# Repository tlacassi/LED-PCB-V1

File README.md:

# LED-PCB-V1

Une vidéo qui explique le minimum nécessaire pour faire tourner l'ESP sur un pcb : https://www.youtube.com/watch?v=tQ0dL_9M1wI&t=242s

Le projet WLED pour le soft et les intégrations : https://kno.wled.ge

Datasheet WS2815b : https://www.marutsu.co.jp/contents/shop/marutsu/datasheet/WS2815B.pdf

Datasheet ESP32 : https://www.espressif.com/sites/default/files/documentation/esp32-s3-wroom-1_wroom-1u_datasheet_en.pdf

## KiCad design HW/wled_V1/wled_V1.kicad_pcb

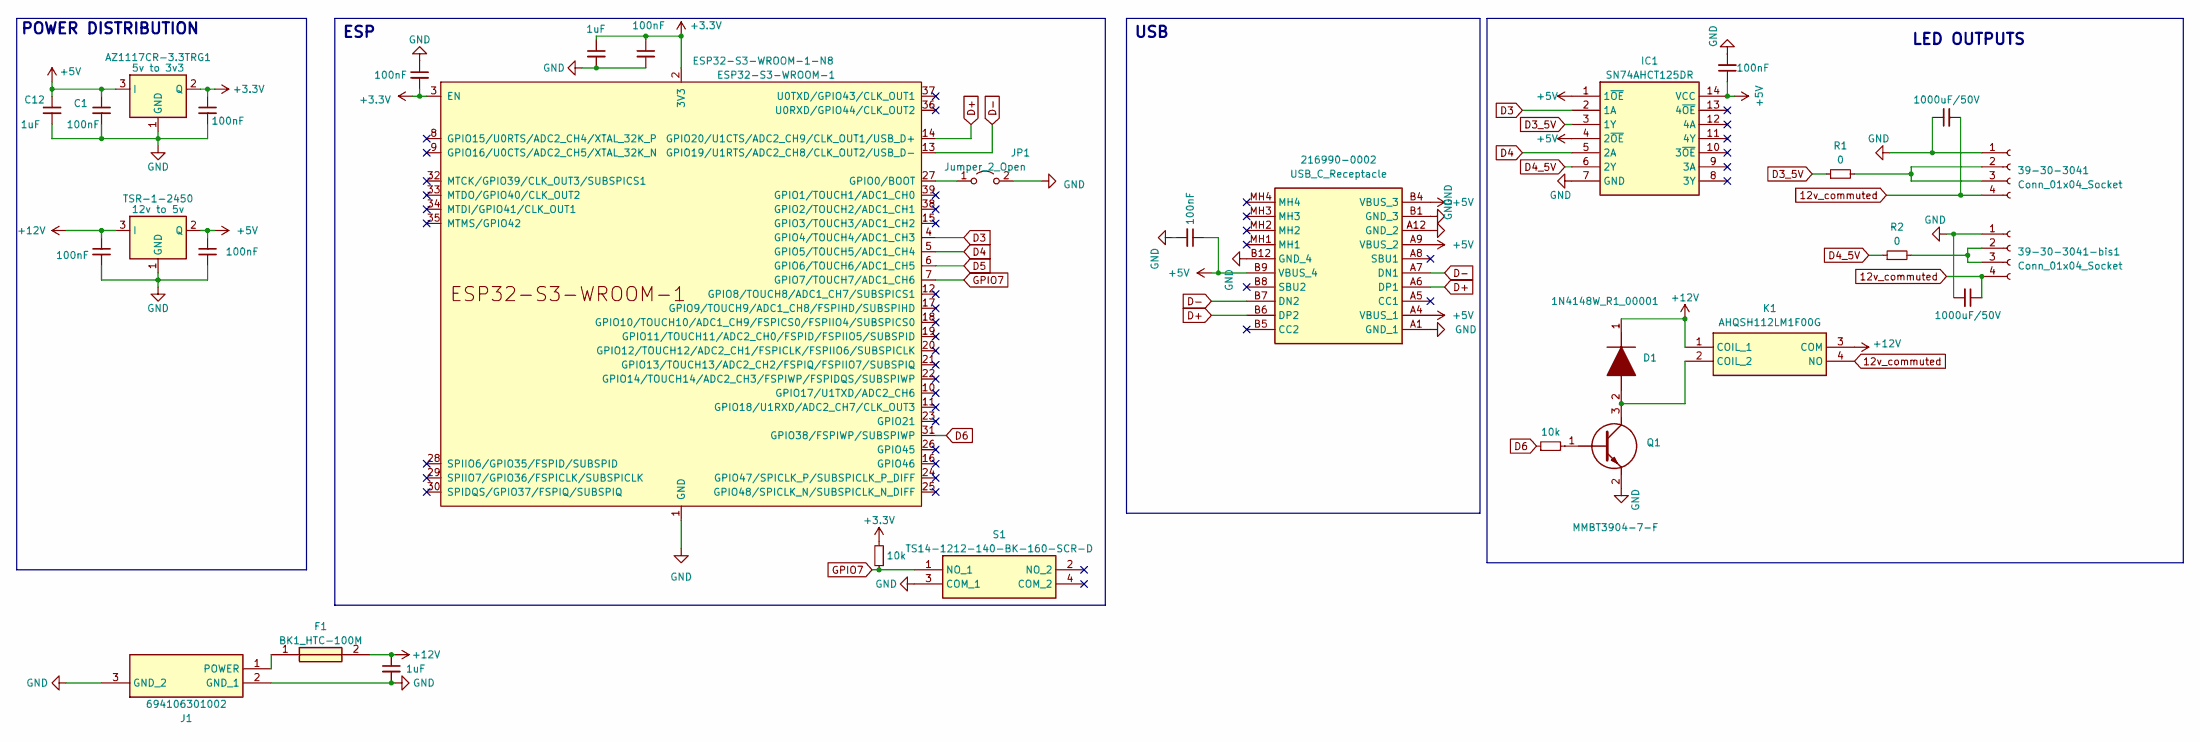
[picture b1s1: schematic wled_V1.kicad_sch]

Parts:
39-30-3041, 39-30-3041-bis1: Conn_01x04_Socket; 39303041
216990-0002: USB_C_Receptacle; 2169900002; Mouser Part Number 538-216990-0002
AZ1117CR-3.3TRG1: 5v to 3v3; AZ1117CR33TRG1
C1, C2, C3, C4, C6, C9, C11, C0402C103K1RACAUTO1: 100nF; CAPC1005X55N
C5, C8: 1000uF/50V; CAPAE1030X1050N
C12, C13, C14: 1uF; CAPC1005X55N
D1: 1N4148W_R1_00001; SOD3816X135N; Mouser Part Number 241-1N4148W_R1_00001
ESP32-S3-WROOM-1-N8: ESP32-S3-WROOM-1; ESP32S3WROOM1N8R8
F1: BK1_HTC-100M; BK1HTC100M; Mouser Part Number 504-BK1-HTC-100M
IC1: SN74AHCT125DR; SOIC127P600X175-14N; Mouser Part Number 595-SN74AHCT125DR
J1: 694106301002; 694106301002_1; Mouser Part Number 710-694106301002
JP1: Jumper_2_Open; SolderJumper-2_P1.3mm_Bridged2Bar_Pad1.0x1.5mm
K1: AHQSH112LM1F00G; Mouser Part Number 523-AHQSH112LM1F00G
Q1: MMBT3904-7-F; SOT96P240X110-3N; Mouser Part Number 621-MMBT3904-F
R1, R2: 0; R_0603_1608Metric_Pad0.98x0.95mm_HandSolder
RN73H1JTTD1002F1, RN73H1JTTD1002F50: 10k; R_0603_1608Metric_Pad0.98x0.95mm_HandSolder
S1: TS14-1212-140-BK-160-SCR-D; TS0266160BK260LCRD; Manufacturer_Part_Number TS14-1212-140-BK-160-SCR-D
TSR-1-2450: 12v to 5v; TSR12450

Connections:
12v_commuted: 39-30-3041.4, 39-30-3041-bis1.4, C5.1, C8.2, K1.4 (NO)
+3.3V: AZ1117CR-3.3TRG1.2 (Q), C2.1, C6.2, C14.1, C0402C103K1RACAUTO1.1, ESP32-S3-WROOM-1-N8.2 (3V3), ESP32-S3-WROOM-1-N8.3 (EN), RN73H1JTTD1002F1.2; also elsewhere on the board
+5V: 216990-0002.A4 (VBUS_1), 216990-0002.A9 (VBUS_2), 216990-0002.B4 (VBUS_3), 216990-0002.B9 (VBUS_4), AZ1117CR-3.3TRG1.3 (I), C1.1, C4.1, C9.1, C11.1, C12.1, IC1.1 (1~OE), IC1.4 (2~OE), IC1.14 (VCC), TSR-1-2450.2 (Q)
+12V: C3.1, C13.1, D1.1 (K), F1.2, K1.1 (COIL_1), K1.3 (COM), TSR-1-2450.3 (I)
D3: ESP32-S3-WROOM-1-N8.4 (GPIO4/TOUCH4/ADC1_CH3), IC1.2 (1A)
D3_5V: IC1.3 (1Y), R1.1
D4: ESP32-S3-WROOM-1-N8.5 (GPIO5/TOUCH5/ADC1_CH4), IC1.5 (2A)
D4_5V: IC1.6 (2Y), R2.1
D5: ESP32-S3-WROOM-1-N8.6 (GPIO6/TOUCH6/ADC1_CH5)
D6: ESP32-S3-WROOM-1-N8.31 (GPIO38/FSPIWP/SUBSPIWP), RN73H1JTTD1002F50.1
D+: 216990-0002.A6 (DP1), 216990-0002.B6 (DP2), ESP32-S3-WROOM-1-N8.14 (GPIO20/U1CTS/ADC2_CH9/CLK_OUT1/USB_D+)
D-: 216990-0002.A7 (DN1), 216990-0002.B7 (DN2), ESP32-S3-WROOM-1-N8.13 (GPIO19/U1RTS/ADC2_CH8/CLK_OUT2/USB_D-)
GND: 39-30-3041.1, 39-30-3041-bis1.1, 216990-0002.A1 (GND_1), 216990-0002.A12 (GND_2), 216990-0002.B1 (GND_3), 216990-0002.B12 (GND_4), AZ1117CR-3.3TRG1.1 (GND), C1.2, C3.2, C4.2, C5.2, C8.1, C9.2, C11.2, C12.2, C13.2, C14.2, C0402C103K1RACAUTO1.2, ESP32-S3-WROOM-1-N8.1 (GND), ESP32-S3-WROOM-1-N8.40 (GND), ESP32-S3-WROOM-1-N8.41 (GND), IC1.7 (GND), J1.2 (GND_1), J1.3 (GND_2), JP1.2 (B), Q1.2 (E), S1.3 (COM_1), TSR-1-2450.1 (GND); also elsewhere on the board
GPIO7: ESP32-S3-WROOM-1-N8.7 (GPIO7/TOUCH7/ADC1_CH6), RN73H1JTTD1002F1.1, S1.1 (NO_1)
unnamed: 39-30-3041.2, 39-30-3041.3, R1.2
unnamed: 39-30-3041-bis1.2, 39-30-3041-bis1.3, R2.2
unnamed: D1.2 (A), K1.2 (COIL_2), Q1.3 (C)
unnamed: ESP32-S3-WROOM-1-N8.27 (GPIO0/BOOT), JP1.1 (A)
unnamed: F1.1, J1.1 (POWER)
unnamed: Q1.1 (B), RN73H1JTTD1002F50.2

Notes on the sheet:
USB
LED OUTPUTS
ESP
POWER DISTRIBUTION

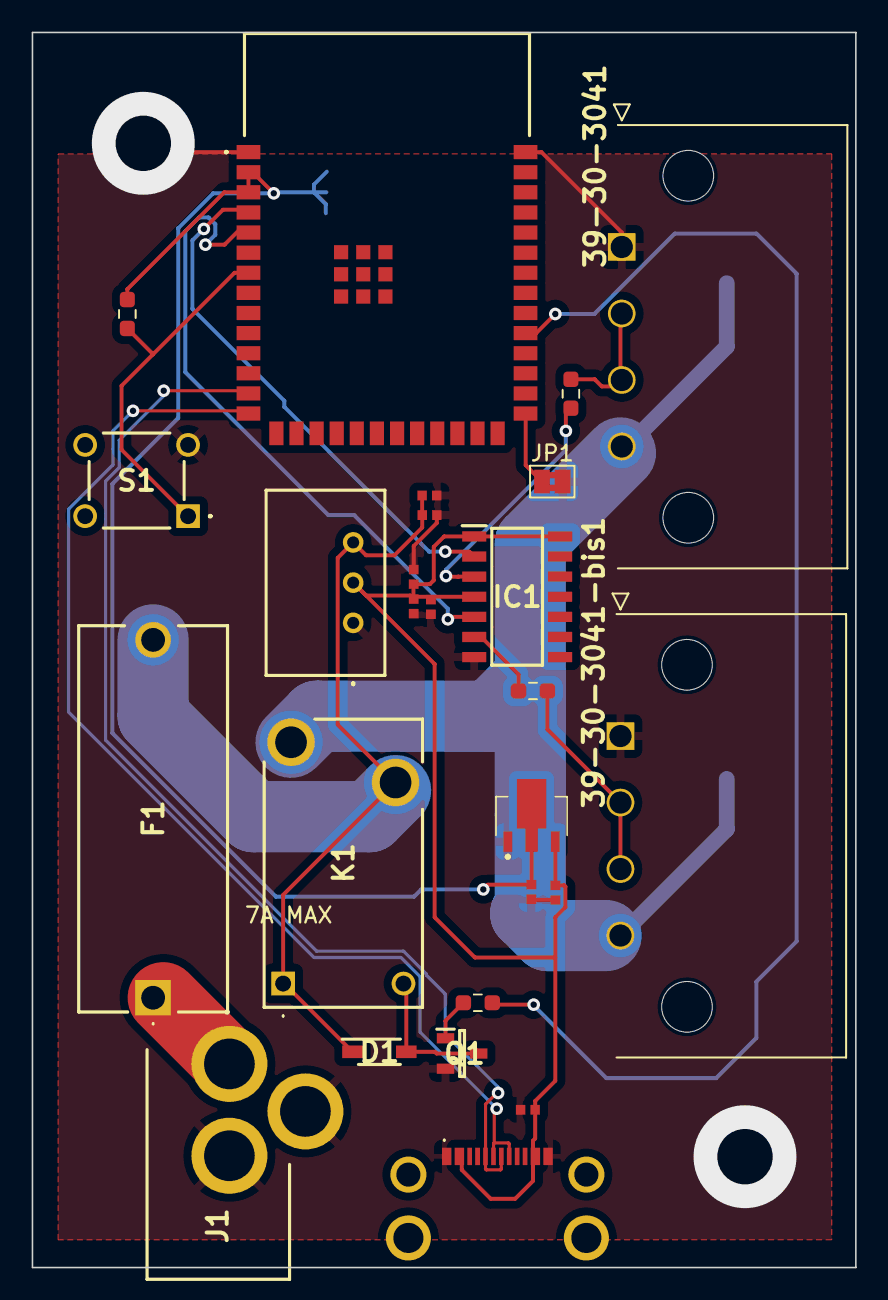
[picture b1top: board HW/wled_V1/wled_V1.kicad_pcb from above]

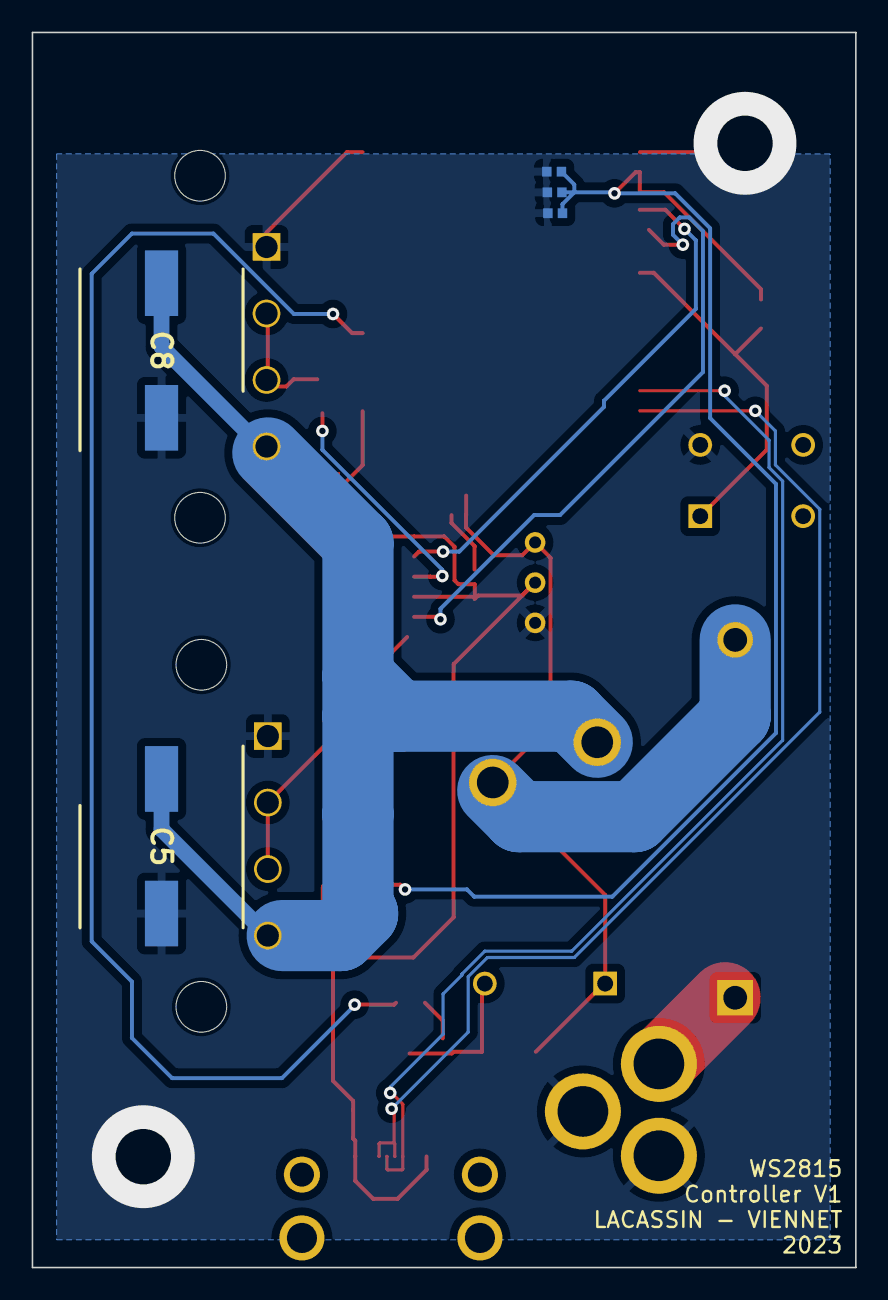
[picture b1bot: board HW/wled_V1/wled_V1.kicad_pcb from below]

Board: 2 copper layers, 52.0 x 78.0 mm, 31 parts (5 on the bottom side), 19 nets.

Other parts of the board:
C10, C15: 100nF; CAPC1005X55N

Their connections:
+3.3V: C10.1, C15.1; also elsewhere on the board
GND: C10.2, C15.2; also elsewhere on the board

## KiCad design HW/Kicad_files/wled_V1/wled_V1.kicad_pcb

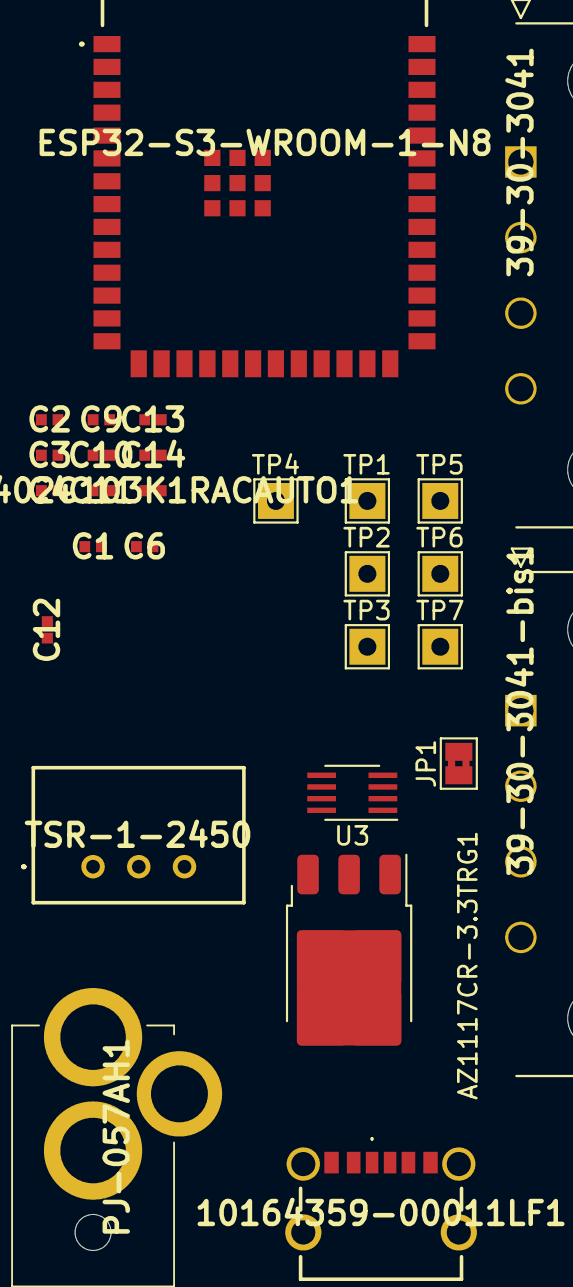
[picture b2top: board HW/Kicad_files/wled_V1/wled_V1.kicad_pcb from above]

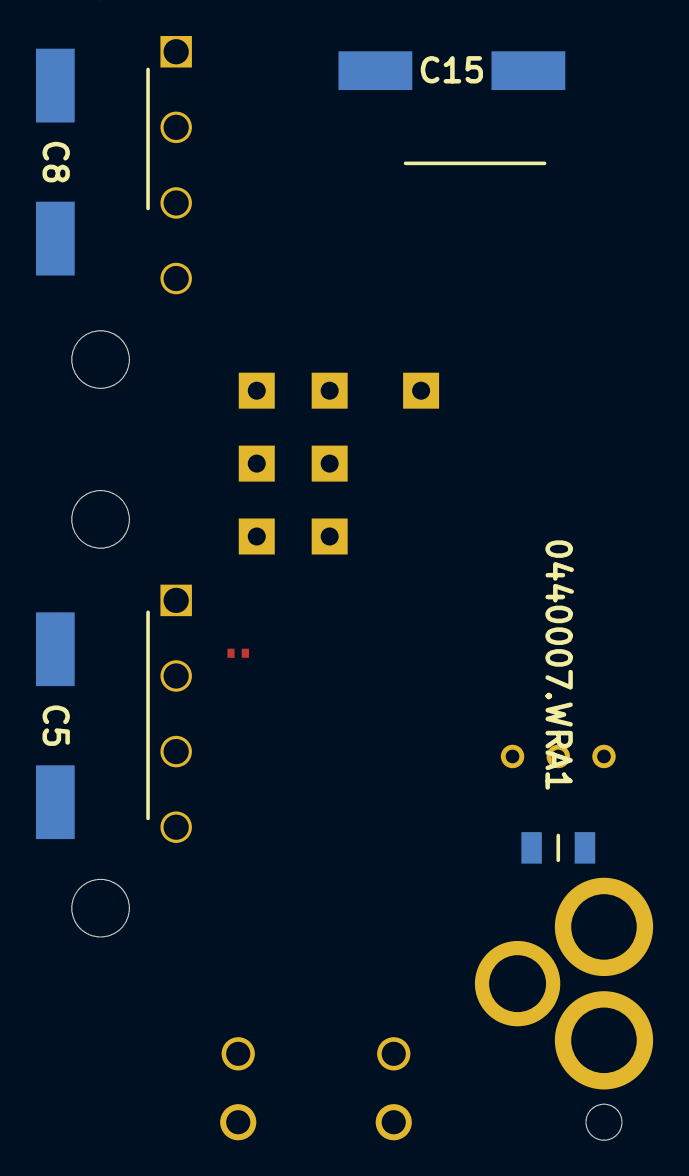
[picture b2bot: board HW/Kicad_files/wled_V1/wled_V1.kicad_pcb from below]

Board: 2 copper layers, 32 parts (4 on the bottom side), 12 nets, no tracks yet.

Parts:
39-30-3041, 39-30-3041-bis1: Conn_01x04_Socket; 39303041
0440007.WRA1: Fuse; FUSC3216X85N
10164359-00011LF1: USB_C_Receptacle; 1016435900011LF
AZ1117CR-3.3TRG1: 5v to 3v3; TO-252-3_TabPin2
C1, C2, C3, C4, C6, C9, C10, C11, C0402C103K1RACAUTO1: 100nF; CAPC1005X55N
C5, C8: 1000uF/50V; CAPAE1030X1030N
C12, C13, C14: 1uF; CAPC1005X55N
C15: 100nF; CAPAE1030X1030N
ESP32-S3-WROOM-1-N8: ESP32-S3-WROOM-1; ESP32S3WROOM1N8R8
JP1: Jumper_2_Open; SolderJumper-2_P1.3mm_Bridged2Bar_Pad1.0x1.5mm
PJ-057AH1: Jack-DC; PJ057AH
TP1, TP2, TP3, TP4, TP5, TP6, TP7: TestPoint; TestPoint_THTPad_2.0x2.0mm_Drill1.0mm
TSR-1-2450: 12v to 5v; TSR12450
U3: TXS0102DCT; SSOP-8_2.95x2.8mm_P0.65mm

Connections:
+3.3V: AZ1117CR-3.3TRG1.2 (Q), C2.1, C6.2, C10.1, C14.1, C15.1, C0402C103K1RACAUTO1.1, ESP32-S3-WROOM-1-N8.2 (3V3), ESP32-S3-WROOM-1-N8.3 (EN), TP2.1, U3.3 (VCCA), U3.6 (OE)
+5V: 10164359-00011LF1.A9 (VBUS), 10164359-00011LF1.B9 (VBUS), AZ1117CR-3.3TRG1.3 (I), C1.1, C4.1, C9.1, C11.1, C12.1, TSR-1-2450.2 (Q), U3.7 (VCCB)
+12V: 39-30-3041.4, 39-30-3041-bis1.4, 0440007.WRA1.2, C3.1, C5.1, C8.2, C13.1, TP1.1, TSR-1-2450.3 (I)
D3: ESP32-S3-WROOM-1-N8.4 (GPIO4/TOUCH4/ADC1_CH3), TP3.1, U3.5 (A1)
D4: ESP32-S3-WROOM-1-N8.5 (GPIO5/TOUCH5/ADC1_CH4), TP4.1, U3.4 (A2)
D5: ESP32-S3-WROOM-1-N8.6 (GPIO6/TOUCH6/ADC1_CH5), TP5.1
D6: ESP32-S3-WROOM-1-N8.7 (GPIO7/TOUCH7/ADC1_CH6), TP6.1
GND: 39-30-3041.1, 39-30-3041-bis1.1, 10164359-00011LF1.A12 (GND), 10164359-00011LF1.B12 (GND), AZ1117CR-3.3TRG1.1 (GND), C1.2, C2.2, C3.2, C4.2, C5.2, C6.1, C8.1, C9.2, C10.2, C11.2, C12.2, C13.2, C14.2, C15.2, C0402C103K1RACAUTO1.2, ESP32-S3-WROOM-1-N8.1 (GND), ESP32-S3-WROOM-1-N8.40 (GND), ESP32-S3-WROOM-1-N8.41 (GND), JP1.2 (B), PJ-057AH1.2, TP7.1, TSR-1-2450.1 (GND), U3.2 (GND)
unnamed: 39-30-3041.2, 39-30-3041.3, U3.8 (B1)
unnamed: 39-30-3041-bis1.2, 39-30-3041-bis1.3, U3.1 (B2)
unnamed: 0440007.WRA1.1, PJ-057AH1.1
unnamed: ESP32-S3-WROOM-1-N8.27 (GPIO0/BOOT), JP1.1 (A)

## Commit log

2023-10-02 ajout schemas kicad
2023-10-02 rename
2023-10-03 5v removed
2023-10-03 untracked
2023-10-03 Power supply update
2023-10-05 Ajout filtrage
2023-10-06 Debut sourcing
2023-10-09 refs updated + lib
2023-10-10 Maj préparation pour sourcing
2023-10-10 routing update
2023-10-10 routing
2023-10-11 supp csv
2023-10-11 sourcing
2023-10-14 routing suite
2023-10-17 nouveau level shifter + emplacement resistors. A router
2023-10-18 ref alternative porte fuse, Théo le zozo va procéder à des mesures de grande importance
2023-10-19 Ajout ref connecteur alim
2023-10-19 new parts and routing
2023-10-19 excel revert
2023-10-19 exported step
2023-10-19 mounting points added
2023-10-20 added relay
2023-10-23 route
2023-10-26 Sourcing maj
